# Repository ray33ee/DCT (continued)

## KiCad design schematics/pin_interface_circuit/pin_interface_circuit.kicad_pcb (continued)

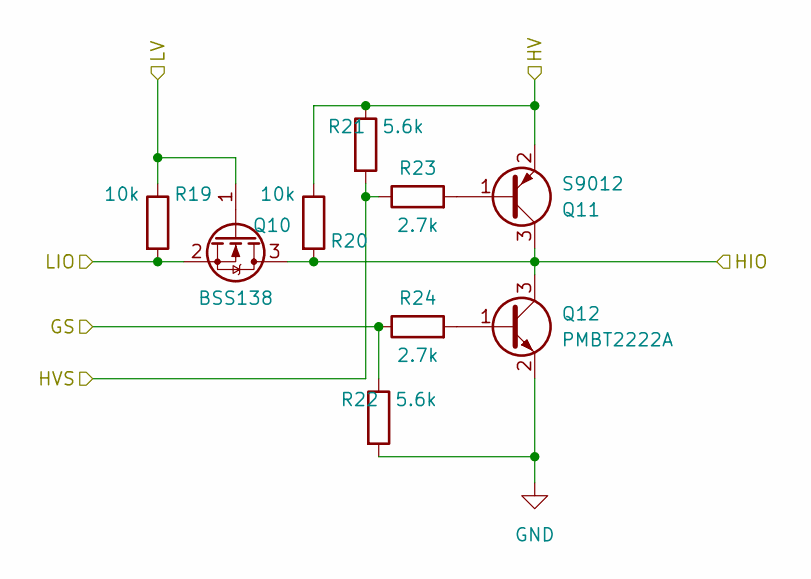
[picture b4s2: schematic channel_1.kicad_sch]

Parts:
Q10: BSS138; SOT-23_Handsoldering
Q11: S9012; SOT-23_Handsoldering
Q12: PMBT2222A; SOT-23_Handsoldering
R19, R20: 10k; R_1206_3216Metric_Pad1.30x1.75mm_HandSolder
R21, R22: 5.6k; R_1206_3216Metric_Pad1.30x1.75mm_HandSolder
R23, R24: 2.7k; R_1206_3216Metric_Pad1.30x1.75mm_HandSolder

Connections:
GND: Q12.2 (E), R22.2; also elsewhere on the board
GS3: R22.1, R24.1; also elsewhere on the board
HIO3: Q10.3 (D), Q11.3 (C), Q12.3 (C), R20.2; also elsewhere on the board
HV: Q11.2 (E), R20.1, R21.1; also elsewhere on the board
HVS3: R21.2, R23.1; also elsewhere on the board
LIO3: Q10.2 (S), R19.2; also elsewhere on the board
LV: Q10.1 (G), R19.1; also elsewhere on the board
unnamed: Q11.1 (B), R23.2
unnamed: Q12.1 (B), R24.2

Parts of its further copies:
Q1, Q4, Q7: BSS138; SOT-23_Handsoldering
Q2, Q5, Q8: S9012; SOT-23_Handsoldering
Q3, Q6, Q9: PMBT2222A; SOT-23_Handsoldering
R1, R2, R7, R8, R13, R14: 10k; R_1206_3216Metric_Pad1.30x1.75mm_HandSolder
R3, R4, R9, R10, R15, R16: 5.6k; R_1206_3216Metric_Pad1.30x1.75mm_HandSolder
R5, R6, R11, R12, R17, R18: 2.7k; R_1206_3216Metric_Pad1.30x1.75mm_HandSolder

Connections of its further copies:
GND: Q3.2 (E), Q6.2 (E), Q9.2 (E), R4.2, R10.2, R16.2; also elsewhere on the board
GS0: R4.1, R6.1; also elsewhere on the board
GS1: R10.1, R12.1; also elsewhere on the board
GS2: R16.1, R18.1; also elsewhere on the board
HIO0: Q1.3 (D), Q2.3 (C), Q3.3 (C), R2.2; also elsewhere on the board
HIO1: Q4.3 (D), Q5.3 (C), Q6.3 (C), R8.2; also elsewhere on the board
HIO2: Q7.3 (D), Q8.3 (C), Q9.3 (C), R14.2; also elsewhere on the board
HV: Q2.2 (E), Q5.2 (E), Q8.2 (E), R2.1, R3.1, R8.1, R9.1, R14.1, R15.1; also elsewhere on the board
HVS0: R3.2, R5.1; also elsewhere on the board
HVS1: R9.2, R11.1; also elsewhere on the board
HVS2: R15.2, R17.1; also elsewhere on the board
LIO0: Q1.2 (S), R1.2; also elsewhere on the board
LIO1: Q4.2 (S), R7.2; also elsewhere on the board
LIO2: Q7.2 (S), R13.2; also elsewhere on the board
LV: Q1.1 (G), Q4.1 (G), Q7.1 (G), R1.1, R7.1, R13.1; also elsewhere on the board
unnamed: Q2.1 (B), R5.2
unnamed: Q3.1 (B), R6.2
unnamed: Q5.1 (B), R11.2
unnamed: Q6.1 (B), R12.2
unnamed: Q8.1 (B), R17.2
unnamed: Q9.1 (B), R18.2

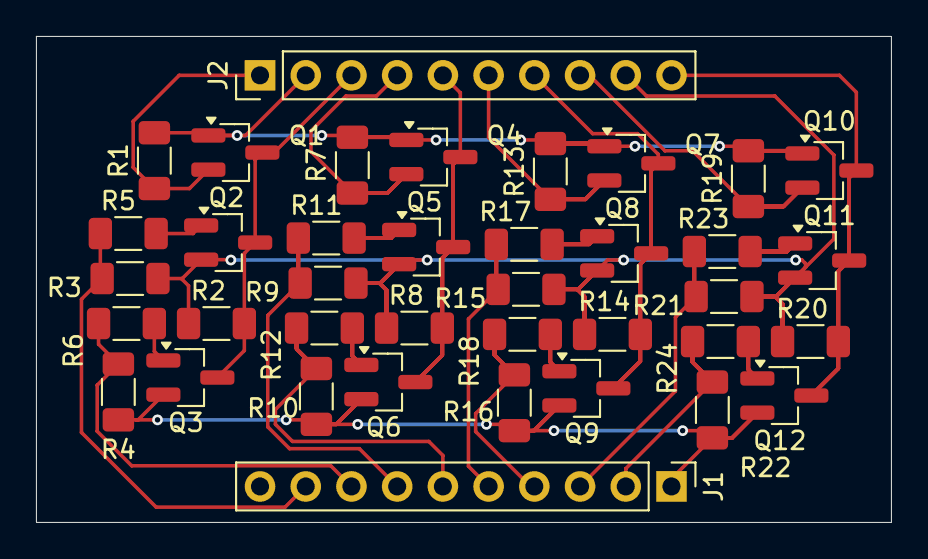
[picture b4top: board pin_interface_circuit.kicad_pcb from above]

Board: 2 copper layers, 47.5 x 27.0 mm, 38 parts (0 on the bottom side), 27 nets.

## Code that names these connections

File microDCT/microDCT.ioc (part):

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Mcu.Name=STM32G474R(B-C-E)Tx
Mcu.Package=LQFP64
Mcu.UserName=STM32G474RETx
PA10.Mode=Full_Duplex_Master
PA10.Signal=SPI2_MISO
PA11.Mode=Full_Duplex_Master
PA11.Signal=SPI2_MOSI
PA13.GPIOParameters=GPIO_Label
PA13.GPIO_Label=T_SWDIO
PA13.Signal=SYS_JTMS-SWDIO
PA14.GPIOParameters=GPIO_Label
PA14.GPIO_Label=T_SWCLK
PA14.Signal=SYS_JTCK-SWCLK
PA15.GPIOParameters=GPIO_Speed,GPIO_Pu
PA15.GPIO_Pu=GPIO_PULLUP
PA15.GPIO_Speed=GPIO_SPEED_FREQ_VERY_HIGH
PA15.Mode=I2C
PA15.Signal=I2C1_SCL
PA2.Mode=Asynchronous
PA2.Signal=USART2_TX
PA3.Mode=Asynchronous
PA3.Signal=USART2_RX
PA5.Signal=S_TIM2_CH1
PA6.Mode=IN3-Differential
PA6.Signal=ADC2_IN3
PA7.Mode=IN3-Differential
PA7.Signal=ADC2_IN4
PA8.Mode=IN1-Single-Ended
PA8.Signal=ADC5_IN1
PB13.Mode=Full_Duplex_Master
PB13.Signal=SPI2_SCK
PB3.GPIOParameters=GPIO_Label
PB3.GPIO_Label=T_SWO
PB3.Signal=SYS_JTDO-SWO
PB7.GPIOParameters=GPIO_Speed,GPIO_Pu,GPIO_FM7
PB7.GPIO_FM7=SYSCFG_FASTMODEPLUS_PB7
PB7.GPIO_Pu=GPIO_PULLUP
PB7.GPIO_Speed=GPIO_SPEED_FREQ_VERY_HIGH
PB7.Mode=I2C
PB7.Signal=I2C1_SDA
PC14-OSC32_IN.GPIOParameters=GPIO_Label
PC14-OSC32_IN.GPIO_Label=RCC_OSC32_IN
PC14-OSC32_IN.Signal=RCC_OSC32_IN
PC15-OSC32_OUT.GPIOParameters=GPIO_Label
PC15-OSC32_OUT.GPIO_Label=RCC_OSC32_OUT
PC15-OSC32_OUT.Signal=RCC_OSC32_OUT
PF0-OSC_IN.GPIOParameters=GPIO_Label
PF0-OSC_IN.GPIO_Label=RCC_OSC_IN
PF0-OSC_IN.Mode=HSE-External-Oscillator
PF0-OSC_IN.Signal=RCC_OSC_IN
PF1-OSC_OUT.GPIOParameters=GPIO_Label
PF1-OSC_OUT.GPIO_Label=RCC_OSC_OUT
PF1-OSC_OUT.Mode=HSE-External-Oscillator
PF1-OSC_OUT.Signal=RCC_OSC_OUT
RCC.HSE_VALUE=48000000
RCC.SYSCLKFreq_VALUE=96000000
RCC.SYSCLKSource=RCC_SYSCLKSOURCE_PLLCLK
board=NUCLEO-G474RE
boardIOC=true

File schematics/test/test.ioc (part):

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Mcu.Name=STM32G474R(B-C-E)Tx
Mcu.Package=LQFP64
Mcu.UserName=STM32G474RETx
PA13.GPIOParameters=GPIO_Label
PA13.GPIO_Label=T_SWDIO
PA13.Signal=SYS_JTMS-SWDIO
PA14.GPIOParameters=GPIO_Label
PA14.GPIO_Label=T_SWCLK
PA14.Signal=SYS_JTCK-SWCLK
PA2.Signal=LPUART1_TX
PA3.Signal=LPUART1_RX
PA5.Signal=GPIO_Output
PB3.GPIOParameters=GPIO_Label
PB3.GPIO_Label=T_SWO
PB3.Signal=SYS_JTDO-SWO
PB5.Signal=GPIO_Output
PB9.Signal=GPIO_Output
PC13.Signal=GPXTI13
PC14-OSC32_IN.GPIOParameters=GPIO_Label
PC14-OSC32_IN.GPIO_Label=RCC_OSC32_IN
PC14-OSC32_IN.Signal=RCC_OSC32_IN
PC15-OSC32_OUT.GPIOParameters=GPIO_Label
PC15-OSC32_OUT.GPIO_Label=RCC_OSC32_OUT
PC15-OSC32_OUT.Signal=RCC_OSC32_OUT
PC7.Signal=GPIO_Output
PD2.Signal=GPIO_Output
PF0-OSC_IN.GPIOParameters=GPIO_Label
PF0-OSC_IN.GPIO_Label=RCC_OSC_IN
PF0-OSC_IN.Signal=RCC_OSC_IN
PF1-OSC_OUT.GPIOParameters=GPIO_Label
PF1-OSC_OUT.GPIO_Label=RCC_OSC_OUT
PF1-OSC_OUT.Signal=RCC_OSC_OUT
RCC.HSE_VALUE=24000000
RCC.SYSCLKFreq_VALUE=170000000
RCC.SYSCLKSource=RCC_SYSCLKSOURCE_PLLCLK
board=NUCLEO-G474RE
boardIOC=true

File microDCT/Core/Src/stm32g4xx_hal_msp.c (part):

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
    __HAL_RCC_GPIOA_CLK_ENABLE();
    /**ADC2 GPIO Configuration
    PA0     ------> ADC2_IN1
    PA1     ------> ADC2_IN2
    PA6     ------> ADC2_IN3
    PA7     ------> ADC2_IN4
    */
    GPIO_InitStruct.Pin = GPIO_PIN_0|GPIO_PIN_1|GPIO_PIN_6|GPIO_PIN_7;
    GPIO_InitStruct.Mode = GPIO_MODE_ANALOG;
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
    __HAL_RCC_GPIOA_CLK_ENABLE();
    /**ADC5 GPIO Configuration
    PA8     ------> ADC5_IN1
    */
    GPIO_InitStruct.Pin = GPIO_PIN_8;
    GPIO_InitStruct.Mode = GPIO_MODE_ANALOG;
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    __HAL_RCC_ADC12_CLK_DISABLE();

    /**ADC2 GPIO Configuration
    PA0     ------> ADC2_IN1
    PA1     ------> ADC2_IN2
    PA6     ------> ADC2_IN3
    PA7     ------> ADC2_IN4
    */
    HAL_GPIO_DeInit(GPIOA, GPIO_PIN_0|GPIO_PIN_1|GPIO_PIN_6|GPIO_PIN_7);

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    __HAL_RCC_ADC345_CLK_DISABLE();

    /**ADC5 GPIO Configuration
    PA8     ------> ADC5_IN1
    */
    HAL_GPIO_DeInit(GPIOA, GPIO_PIN_8);

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    __HAL_RCC_GPIOA_CLK_ENABLE();
    __HAL_RCC_GPIOB_CLK_ENABLE();
    /**I2C1 GPIO Configuration
    PA15     ------> I2C1_SCL
    PB7     ------> I2C1_SDA
    */
    GPIO_InitStruct.Pin = GPIO_PIN_15;
    GPIO_InitStruct.Mode = GPIO_MODE_AF_OD;
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    __HAL_RCC_I2C1_CLK_DISABLE();

    /**I2C1 GPIO Configuration
    PA15     ------> I2C1_SCL
    PB7     ------> I2C1_SDA
    */
    HAL_GPIO_DeInit(GPIOA, GPIO_PIN_15);

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
    __HAL_RCC_GPIOA_CLK_ENABLE();
    /**TIM2 GPIO Configuration
    PA5     ------> TIM2_CH1
    */
    GPIO_InitStruct.Pin = GPIO_PIN_5;
    GPIO_InitStruct.Mode = GPIO_MODE_AF_PP;
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
    __HAL_RCC_GPIOA_CLK_ENABLE();
    /**USART2 GPIO Configuration
    PA2     ------> USART2_TX
    PA3     ------> USART2_RX
    */
    GPIO_InitStruct.Pin = GPIO_PIN_2|GPIO_PIN_3;
    GPIO_InitStruct.Mode = GPIO_MODE_AF_PP;
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    __HAL_RCC_USART2_CLK_DISABLE();

    /**USART2 GPIO Configuration
    PA2     ------> USART2_TX
    PA3     ------> USART2_RX
    */
    HAL_GPIO_DeInit(GPIOA, GPIO_PIN_2|GPIO_PIN_3);

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
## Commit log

2025-07-12 added host controller program
